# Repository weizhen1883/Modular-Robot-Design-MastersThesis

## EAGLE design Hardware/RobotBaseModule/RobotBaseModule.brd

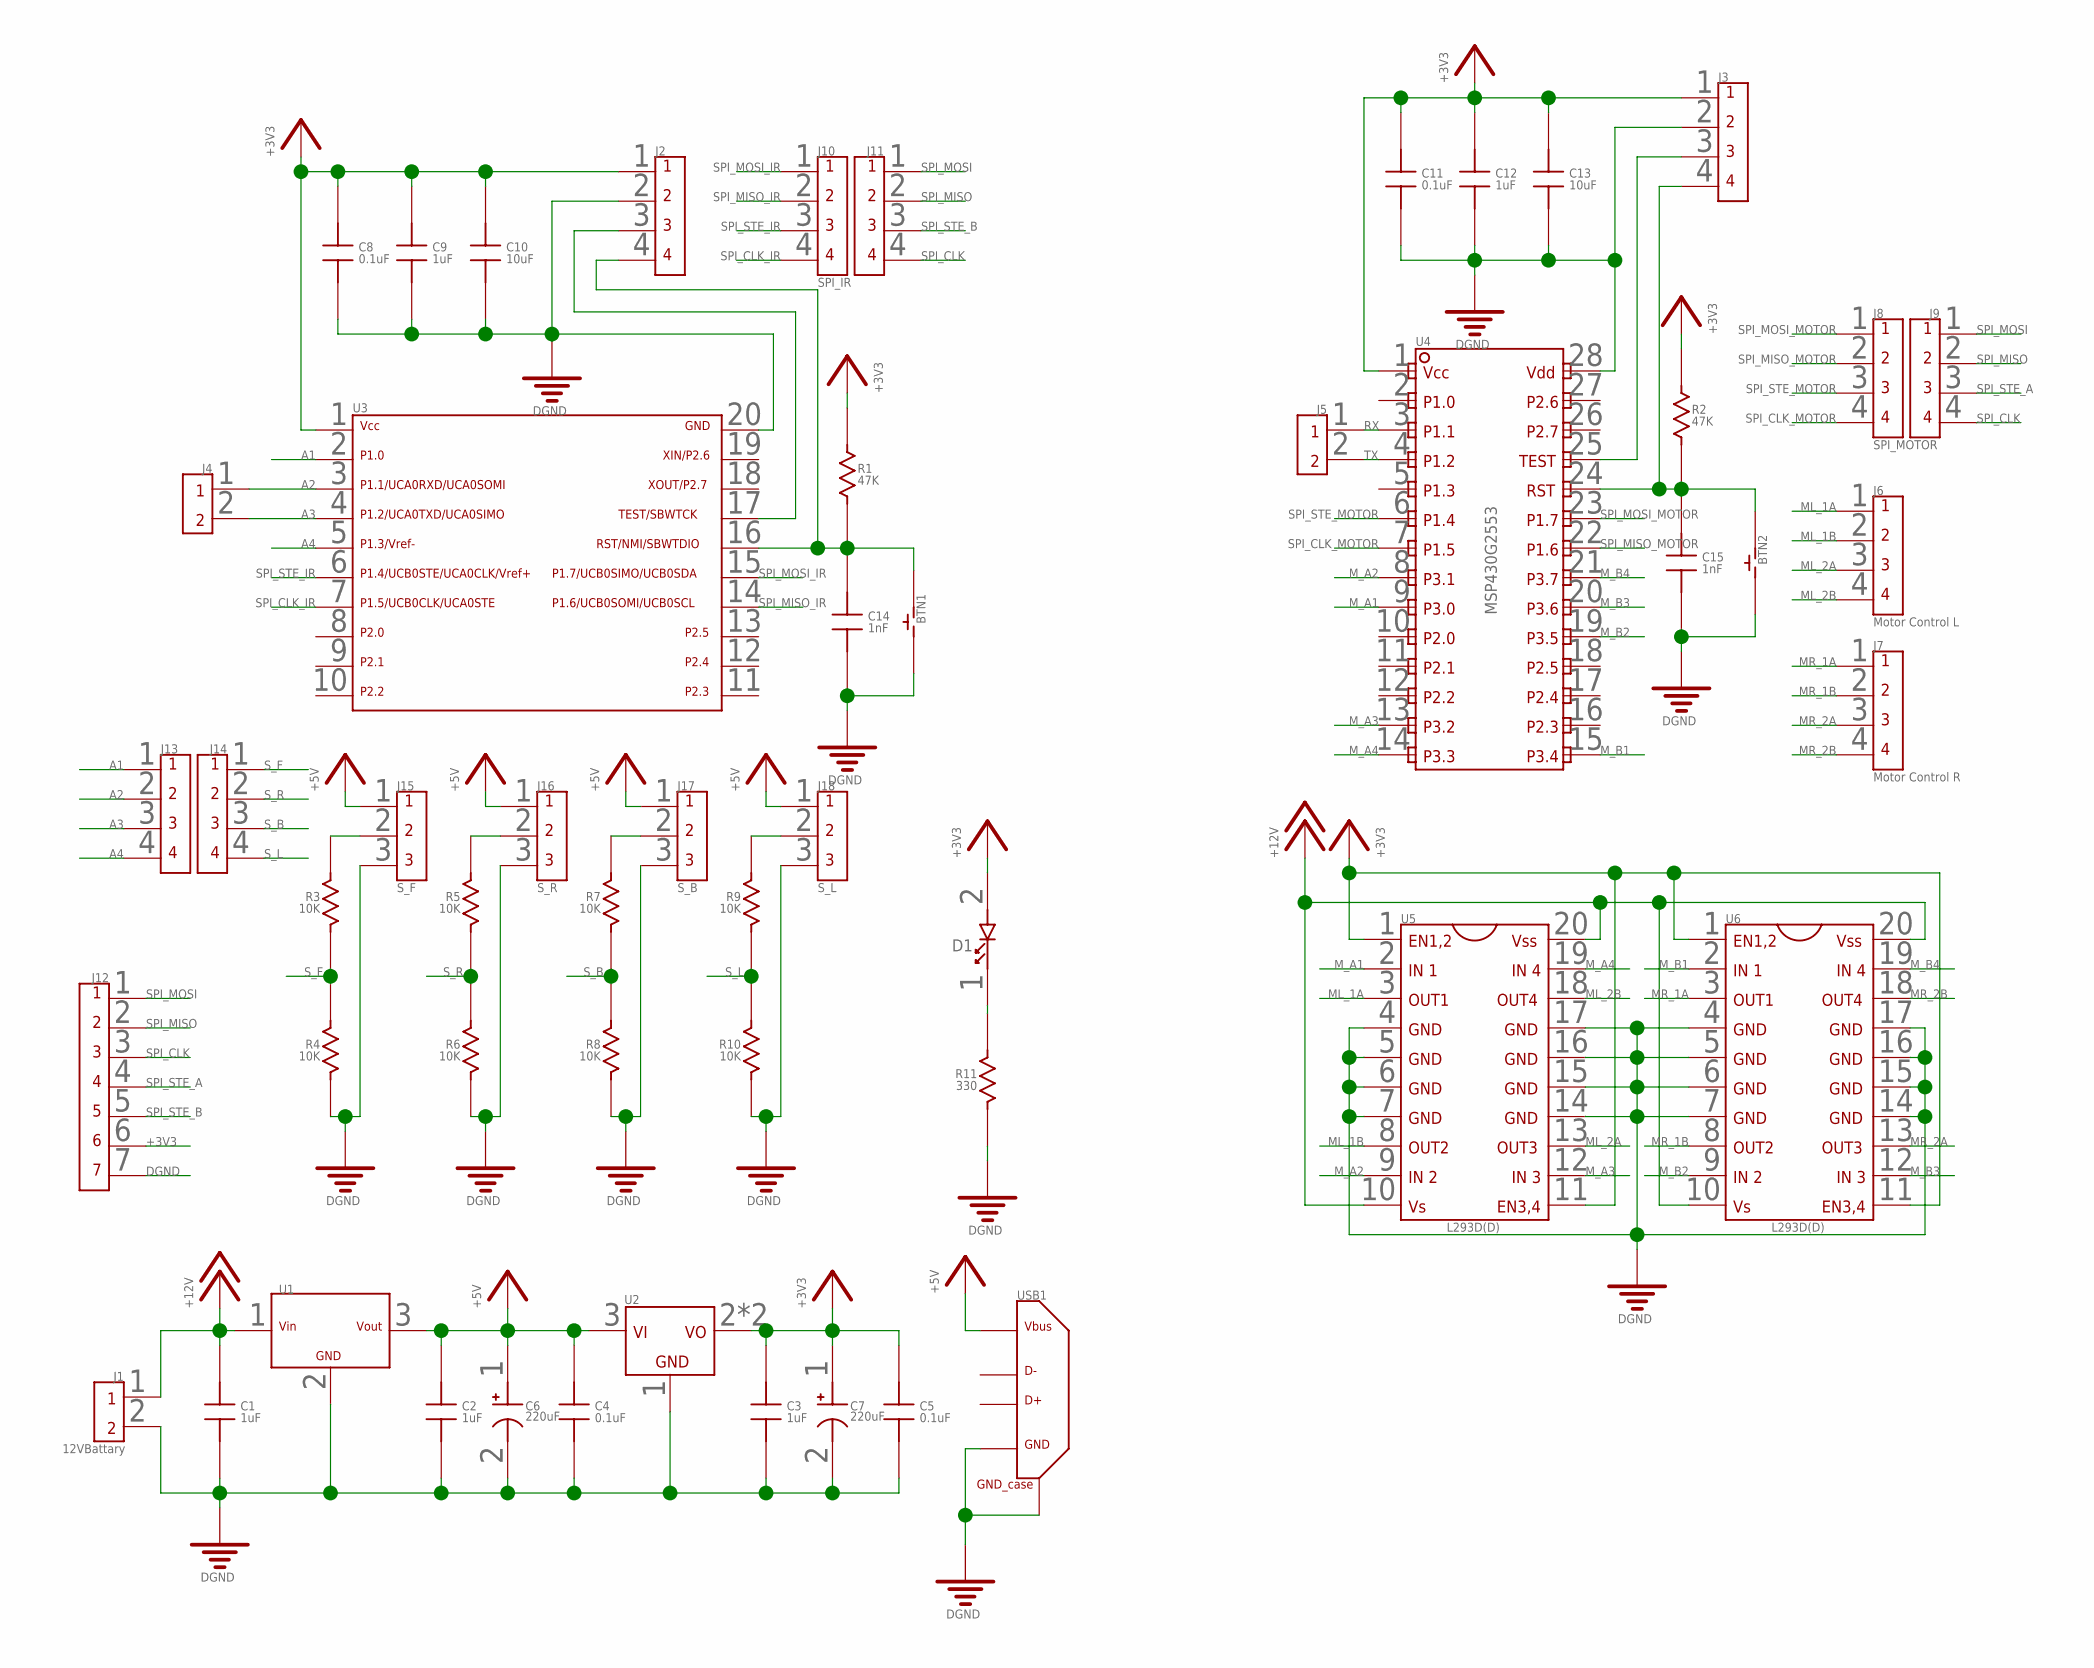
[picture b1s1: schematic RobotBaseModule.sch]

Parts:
BTN1, BTN2: BTN_NORMAL_OFF_6_3.5_SMD; BTN_6_3.5_SMD
C1, C2, C3, C9, C12: 1uF; 0805
C4, C5, C8, C11: 0.1uF; 0805
C6, C7: 220uF; CAP_830_830
C10, C13: 10uF; 0805
C14, C15: 1nF; 0805
D1: LED_0805; 0805DIODE
J1: 12VBattary; 2PIN_TERMBLOCK_PITCH5.08MM
J2, J3: 4PIN_HEADER_VERT_PITCH2.54MM_TH
J4, J5: 2PIN_HEADER_PITCH2.54MM_TH
J6: Motor Control L; 4PIN_HEADER_VERT_PITCH2.54MM_TH
J7: Motor Control R; 4PIN_HEADER_VERT_PITCH2.54MM_TH
J8: SPI_MOTOR; 4PIN_HEADER_PITCH2.54MM_TH
J9, J11, J13, J14: 4PIN_HEADER_PITCH2.54MM_TH
J10: SPI_IR; 4PIN_HEADER_PITCH2.54MM_TH
J12: 7PIN_HEADER_VERT_PITCH2.54MM_TH
J15: S_F; 3PIN_HEADER_VERT_PITCH2.54MM_TH
J16: S_R; 3PIN_HEADER_VERT_PITCH2.54MM_TH
J17: S_B; 3PIN_HEADER_VERT_PITCH2.54MM_TH
J18: S_L; 3PIN_HEADER_VERT_PITCH2.54MM_TH
R1, R2: 47K; 0805
R3, R4, R5, R6, R7, R8, R9, R10: 10K; 0805
R11: 330; 0805
U1: V78-2000R
U2: LM1117_SOT-223-4; SOT-233-4
U3: MSP430G2X53/G2X13_SSOP20; SSOP-20
U4: MSP430G2553; TSSOP-28
U5, U6: L293D(D)_ST_SMD; SOIC_20
USB1: USB-1.X/2.0-STANDARDTYPEA-TH; USB-A-TH

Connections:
+3V3: C3.1, C5.1, C7.1, C8.1, C9.1, C10.1, C11.1, C12.1, C13.1, D1.2, J2.1, J3.1, J12.6, R1.1, R2.1, U2.2 (VOUT), U2.4 (VOUT), U3.1, U4.1, U5.1, U5.11, U6.1, U6.11
+5V: C2.1, C4.1, C6.1, J15.1, J16.1, J17.1, J18.1, U1.3 (VOUT), U2.3 (VIN), USB1.1 (VBUS)
+12V: C1.1, J1.1, U1.1 (VIN), U5.10, U5.20, U6.10, U6.20
A1: J13.1, U3.2
A2: J4.1, J13.2, U3.3
A3: J4.2, J13.3, U3.4
A4: J13.4, U3.5
DGND: BTN1.2, BTN2.2, C1.2, C2.2, C3.2, C4.2, C5.2, C6.2, C7.2, C8.2, C9.2, C10.2, C11.2, C12.2, C13.2, C14.2, C15.2, J1.2, J2.2, J3.2, J12.7, J15.3, J16.3, J17.3, J18.3, R4.2, R6.2, R8.2, R10.2, R11.2, U1.2 (GND), U2.1 (GND), U3.20, U4.28, U5.4, U5.5, U5.6, U5.7, U5.14, U5.15, U5.16, U5.17, U6.4, U6.5, U6.6, U6.7, U6.14, U6.15, U6.16, U6.17, USB1.4 (GND), USB1.CASE1 (GND_CASE), USB1.CASE2 (GND_CASE)
ML_1A: J6.1, U5.3
ML_1B: J6.2, U5.8
ML_2A: J6.3, U5.13
ML_2B: J6.4, U5.18
MR_1A: J7.1, U6.3
MR_1B: J7.2, U6.8
MR_2A: J7.3, U6.13
MR_2B: J7.4, U6.18
M_A1: U4.9, U5.2
M_A2: U4.8, U5.9
M_A3: U4.13, U5.12
M_A4: U4.14, U5.19
M_B1: U4.15, U6.2
M_B2: U4.19, U6.9
M_B3: U4.20, U6.12
M_B4: U4.21, U6.19
unnamed: J3.3, U4.25
unnamed: J2.3, U3.17
unnamed: BTN1.1, C14.1, J2.4, R1.2, U3.16
unnamed: BTN2.1, C15.1, J3.4, R2.2, U4.24
unnamed: J15.2, R3.1
unnamed: D1.1, R11.1
unnamed: J16.2, R5.1
unnamed: J17.2, R7.1
unnamed: J18.2, R9.1
RX: J5.1, U4.3
SPI_CLK: J9.4, J11.4, J12.3
SPI_CLK_IR: J10.4, U3.7
SPI_CLK_MOTOR: J8.4, U4.7
SPI_MISO: J9.2, J11.2, J12.2
SPI_MISO_IR: J10.2, U3.14
SPI_MISO_MOTOR: J8.2, U4.22
SPI_MOSI: J9.1, J11.1, J12.1
SPI_MOSI_IR: J10.1, U3.15
SPI_MOSI_MOTOR: J8.1, U4.23
SPI_STE_A: J9.3, J12.4
SPI_STE_B: J11.3, J12.5
SPI_STE_IR: J10.3, U3.6
SPI_STE_MOTOR: J8.3, U4.6
S_B: J14.3, R7.2, R8.1
S_F: J14.1, R3.2, R4.1
S_L: J14.4, R9.2, R10.1
S_R: J14.2, R5.2, R6.1
TX: J5.2, U4.4

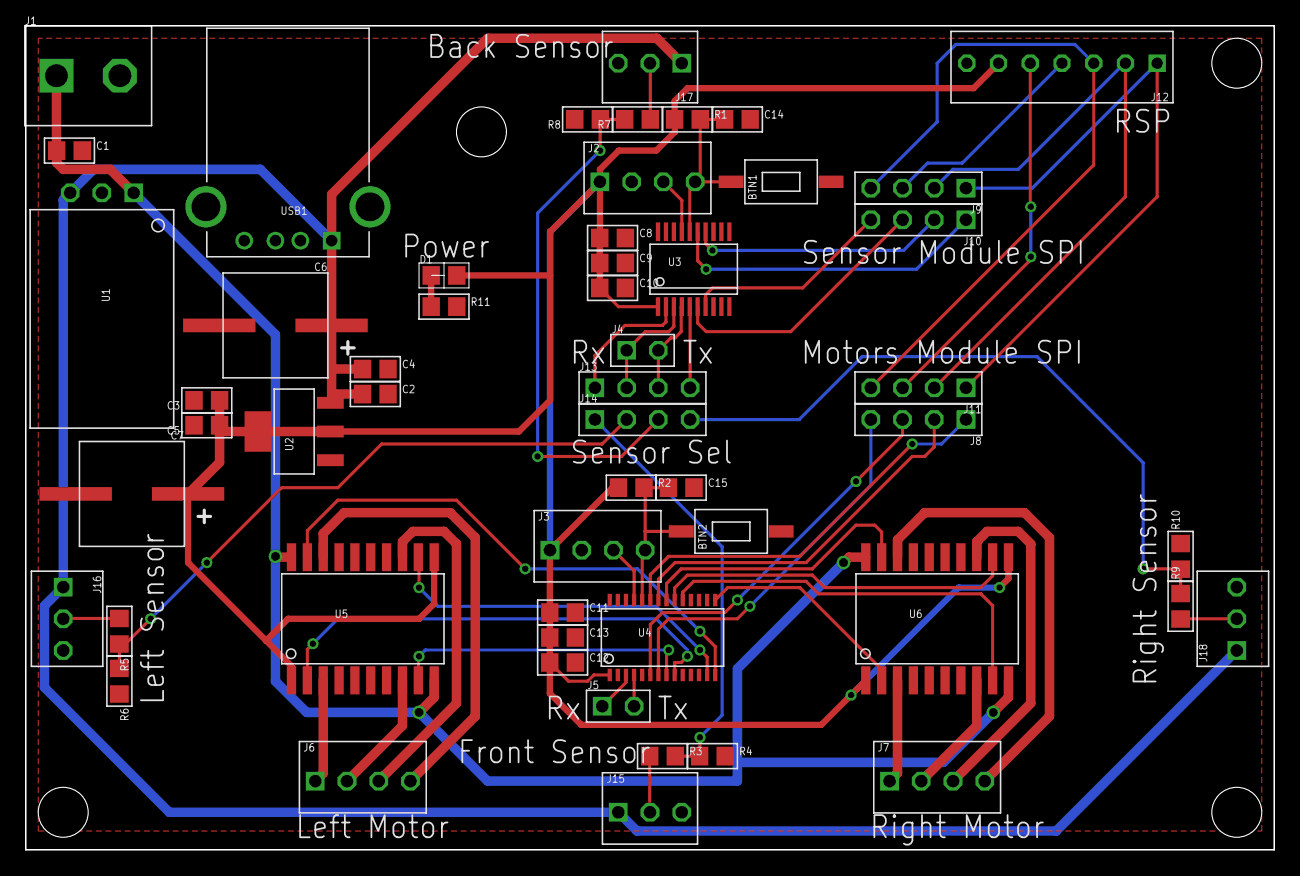
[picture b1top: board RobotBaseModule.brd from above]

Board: 2 copper layers, 100.0 x 66.0 mm, 54 parts (0 on the bottom side), 52 nets.

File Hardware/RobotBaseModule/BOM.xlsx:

Parts | Value | Footprint | Parts Number | Price | Quantity | Total
C1,C2,C3,C9,C12 | 1uF | 0805 | CL21F105ZOCNNNC | 0.1 | 5 | 0.5
C4,C5,C8,C11 | 0.1uF | 0805 | CL21F104ZBCNNNC | 0.1 | 4 | 0.4
C10,C13 | 10uF | 0805 | CL21F106ZQFNNNE | 0.14000000000000001 | 2 | 0.28000000000000003
C14,C15 | 1nF | 0805 | CL21C102JBCNNNC | 0.1 | 2 | 0.2
C6,C7 | 220uF | CAP830*830 | UWX0J221MCL1GB | 0.34 | 2 | 0.68
R1,R2 | 47KΩ | 0805 | RC2012F473CS | 0.1 | 2 | 0.2
R3,R4,R5,R6,R7,R8,R9,R10 | 10KΩ | 0805 | RC0805JR-0710KL | 0.1 | 8 | 0.8
R11 | 330Ω | 0805 | RC2012F331CS | 0.1 | 1 | 0.1
D1 |  | 0805 | LG R971-KN-1 | 0.26 | 1 | 0.26
U1 | V7805-2000R | V78-2000R | V7805-2000R | 10.84 | 1 | 10.84
U2 | LM1117-3.3V | SOT-233-4 | LM1117IMPX-3.3/NOPB | 1.04 | 1 | 1.04
U3 | MSP430G2553 | SSOP-20 | MSP430G2553IPW20R | 2.46 | 1 | 2.46
U4 | MSP430G2553 | TSSOP-28 | MSP430G2553IPW28R | 2.73 | 1 | 2.73
U5,U6 | L293DD | SOIC_20 | L293DD | 3.44 | 2 | 6.88
BTN1,BTN2 | SPST SMD | 6*3.5 |  | 0.15 | 2 | 0.3
USB1 | USB1.X/2.0 Standard TypeA TH | USB-A-TH |  | 0.1 | 1 | 0.1
J1 | 2pin 0.200" terminal block | 2PIN_TERMBLOCK_PITCH5.08MM | 1935161 | 0.37 | 1 | 0.37
J2,J3,J6,J7 | 4pin 0.100" header (single dir) | 4PIN_HEADER_VERT_PITCH2.54MM | 640454-4 | 0.18 | 4 | 0.72
J4,J5 | 2pin 0.100" header | 2PIN_HEADER_PITCH2.54MM |  | 0.1 | 2 | 0.2
J8,J9,J10,J11,J13,J14 | 4pin 0.100" header | 4PIN_HEADER_PITCH2.54MM |  | 0.1 | 6 | 0.60000000000000009
J12 | 7pin 0.100" header (single dir) | 7PIN_HEADER_VERT_PITCH2.54MM | 640456-7 | 0.27 | 1 | 0.27
J15,J16,J17,J18 | 3pin 0.100" header (single dir) | 3PIN_HEADER_VERT_PITCH2.54MM | 640454-3 | 0.16 | 1 | 0.16
 | CONN HOUS 3POS 0.100 |  | 0022013037 | 0.19 | 4 | 0.76
 | CONN HOUS 4POS 0.100 |  | 0022013047 | 0.2 | 4 | 0.8
 | CONN HOUS 7POS 0.100 |  | 0022013077 | 0.36 | 1 | 0.36
 |  |  |  |  | Total: | 29.19

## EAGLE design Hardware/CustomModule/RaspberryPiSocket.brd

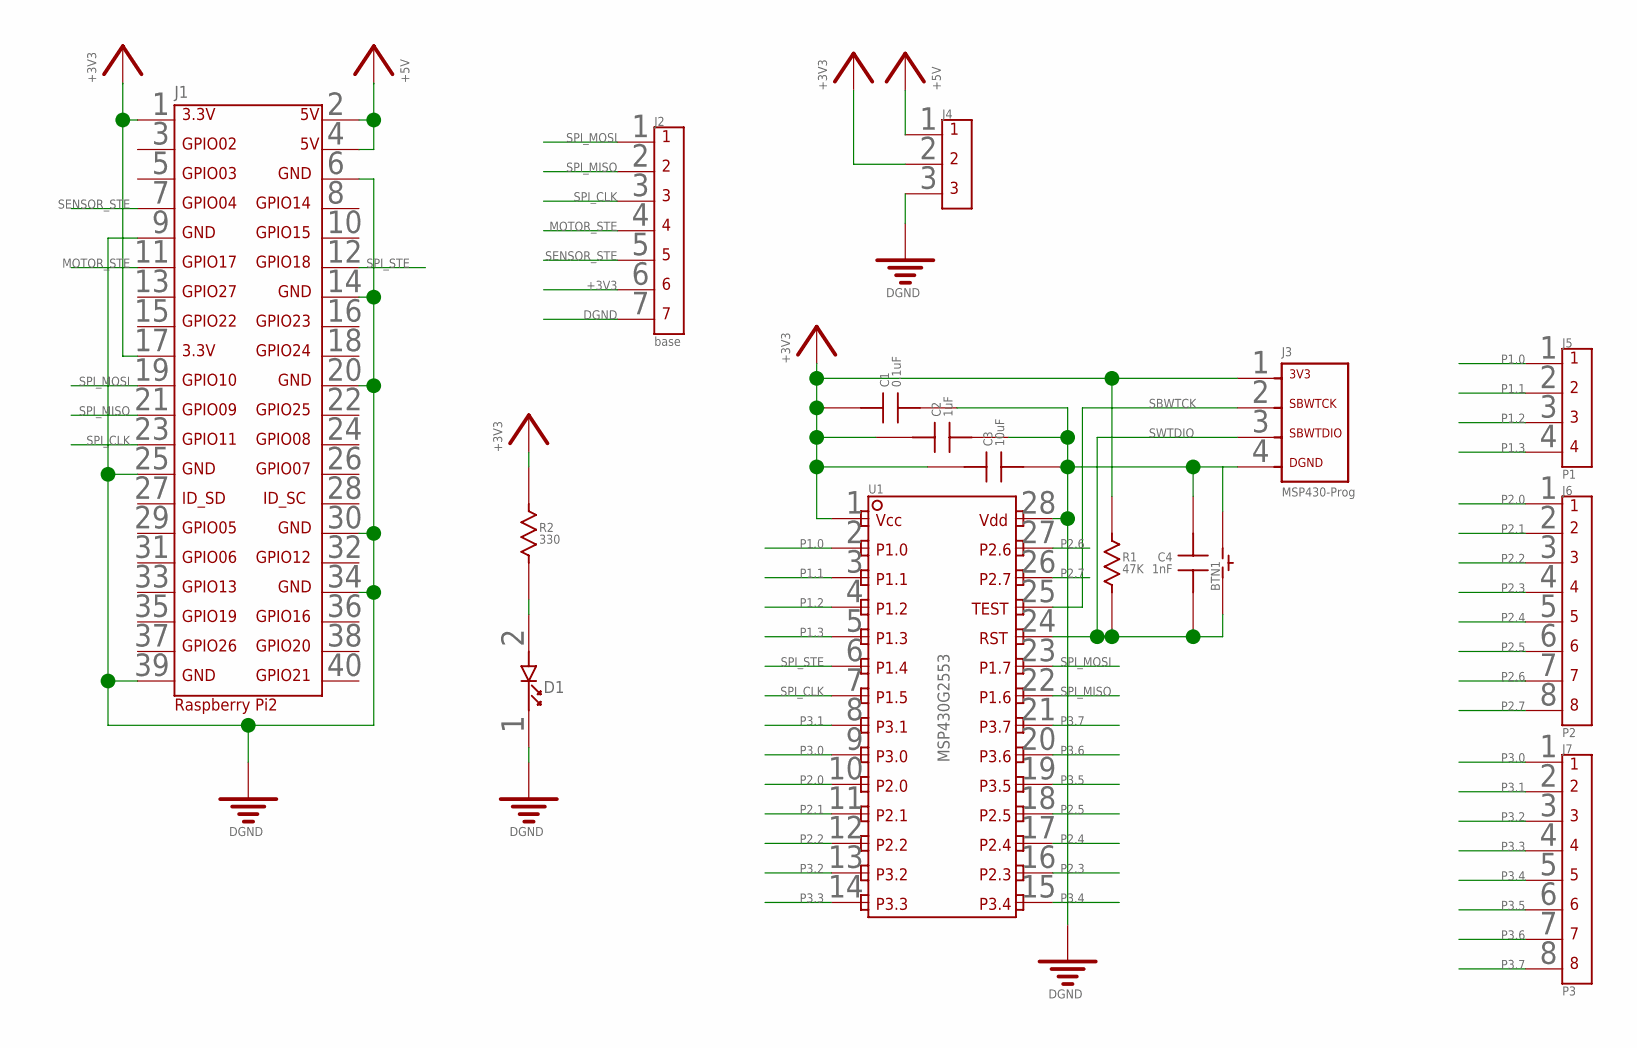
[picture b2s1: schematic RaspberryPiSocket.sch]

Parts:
BTN1: BTN_NORMAL_OFF_6_3.5_SMD; BTN_6_3.5_SMD
C1: 0.1uF; 0805
C2: 1uF; 0805
C3: 10uF; 0805
C4: 1nF; 0805
D1: LED_0805; 0805DIODE
J1: RPI2
J2: base; 7PIN_HEADER_VERT_PITCH2.54MM_TH
J3: MSP430-PROG_NORMAL; 4PIN_HEADER_PITCH2.54MM_TH
J4: 3PIN_HEADER_PITCH2.54MM_TH
J5: P1; 4PIN_HEADER_PITCH2.54MM_TH
J6: P2; 8PIN_HEADER_PITCH2.54MM_TH
J7: P3; 8PIN_HEADER_PITCH2.54MM_TH
R1: 47K; 0805
R2: 330; 0805
U1: MSP430G2553_24IO_28PIN_TSSOP; TSSOP-28

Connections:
+3V3: C1.1, C2.1, C3.1, J1.1, J1.17, J2.6, J3.1, J4.2, R1.1, R2.1, U1.1
+5V: J1.2, J1.4, J4.1
DGND: BTN1.2, C1.2, C2.2, C3.2, C4.1, D1.1, J1.6, J1.9, J1.14, J1.20, J1.25, J1.30, J1.34, J1.39, J2.7, J3.4, J4.3, U1.28
MOTOR_STE: J1.11, J2.4
unnamed: D1.2, R2.2
P1.0: J5.1, U1.2
P1.1: J5.2, U1.3
P1.2: J5.3, U1.4
P1.3: J5.4, U1.5
P2.0: J6.1, U1.10
P2.1: J6.2, U1.11
P2.2: J6.3, U1.12
P2.3: J6.4, U1.16
P2.4: J6.5, U1.17
P2.5: J6.6, U1.18
P2.6: J6.7, U1.27
P2.7: J6.8, U1.26
P3.0: J7.1, U1.9
P3.1: J7.2, U1.8
P3.2: J7.3, U1.13
P3.3: J7.4, U1.14
P3.4: J7.5, U1.15
P3.5: J7.6, U1.19
P3.6: J7.7, U1.20
P3.7: J7.8, U1.21
SBWTCK: J3.2, U1.25
SENSOR_STE: J1.7, J2.5
SPI_CLK: J1.23, J2.3, U1.7
SPI_MISO: J1.21, J2.2, U1.22
SPI_MOSI: J1.19, J2.1, U1.23
SPI_STE: J1.12, U1.6
SWTDIO: BTN1.1, C4.2, J3.3, R1.2, U1.24

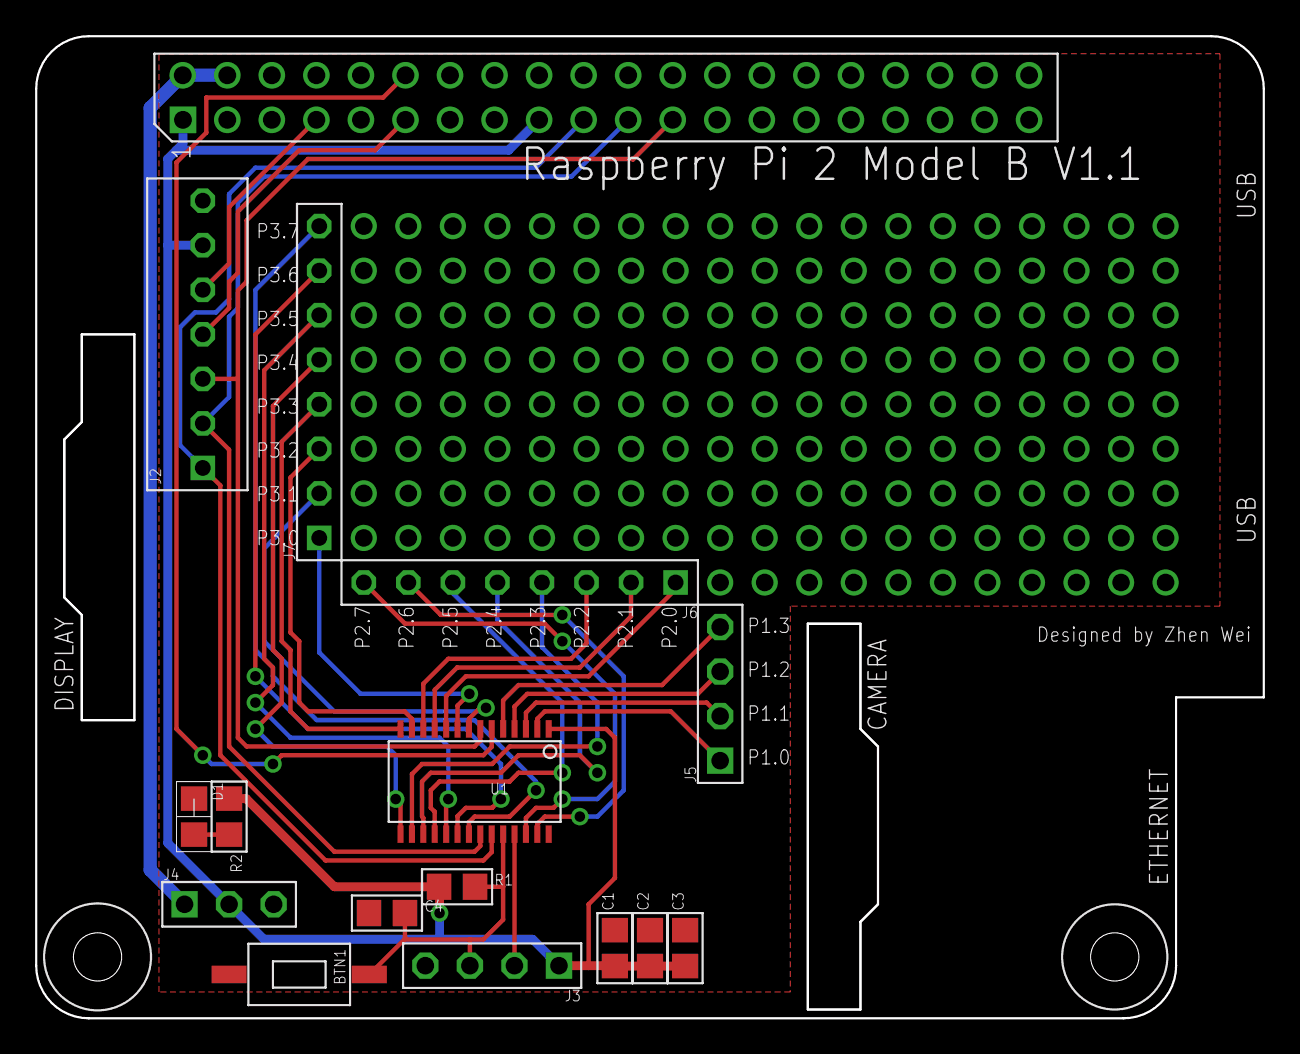
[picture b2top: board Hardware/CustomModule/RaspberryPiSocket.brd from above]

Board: 2 copper layers, 70.0 x 56.0 mm, 16 parts (0 on the bottom side), 32 nets.

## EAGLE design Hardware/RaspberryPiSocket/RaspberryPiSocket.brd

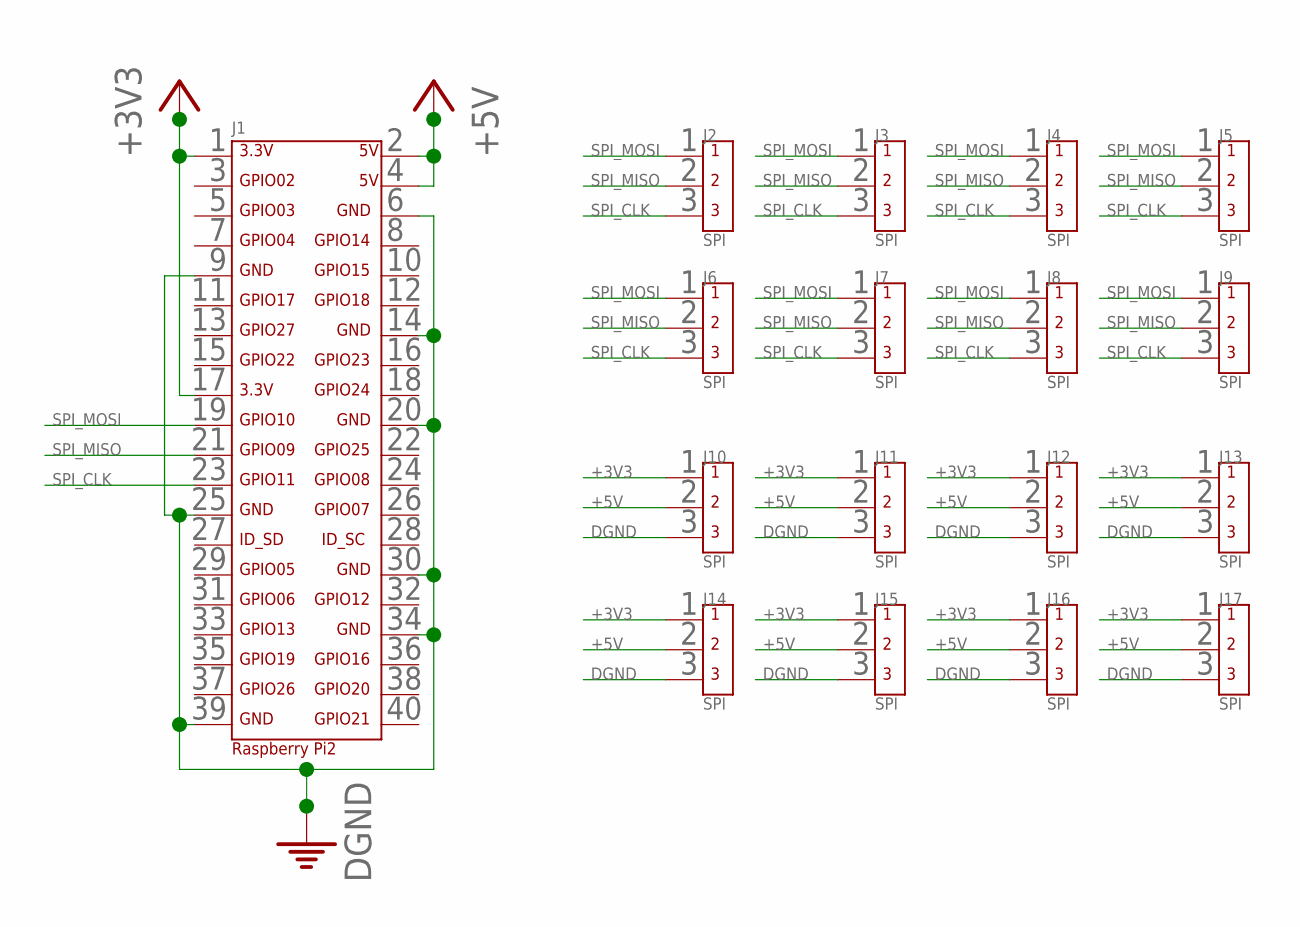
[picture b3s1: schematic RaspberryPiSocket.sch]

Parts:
J1: RPI2
J2, J3, J4, J5, J6, J7, J8, J9, J10, J11, J12, J13, J14, J15, J16, J17: SPI; CON_HEADER_3_100

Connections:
+3V3: J1.1, J1.17, J10.1, J11.1, J12.1, J13.1, J14.1, J15.1, J16.1, J17.1
+5V: J1.2, J1.4, J10.2, J11.2, J12.2, J13.2, J14.2, J15.2, J16.2, J17.2
DGND: J1.6, J1.9, J1.14, J1.20, J1.25, J1.30, J1.34, J1.39, J10.3, J11.3, J12.3, J13.3, J14.3, J15.3, J16.3, J17.3
SPI_CLK: J1.23, J2.3, J3.3, J4.3, J5.3, J6.3, J7.3, J8.3, J9.3
SPI_MISO: J1.21, J2.2, J3.2, J4.2, J5.2, J6.2, J7.2, J8.2, J9.2
SPI_MOSI: J1.19, J2.1, J3.1, J4.1, J5.1, J6.1, J7.1, J8.1, J9.1

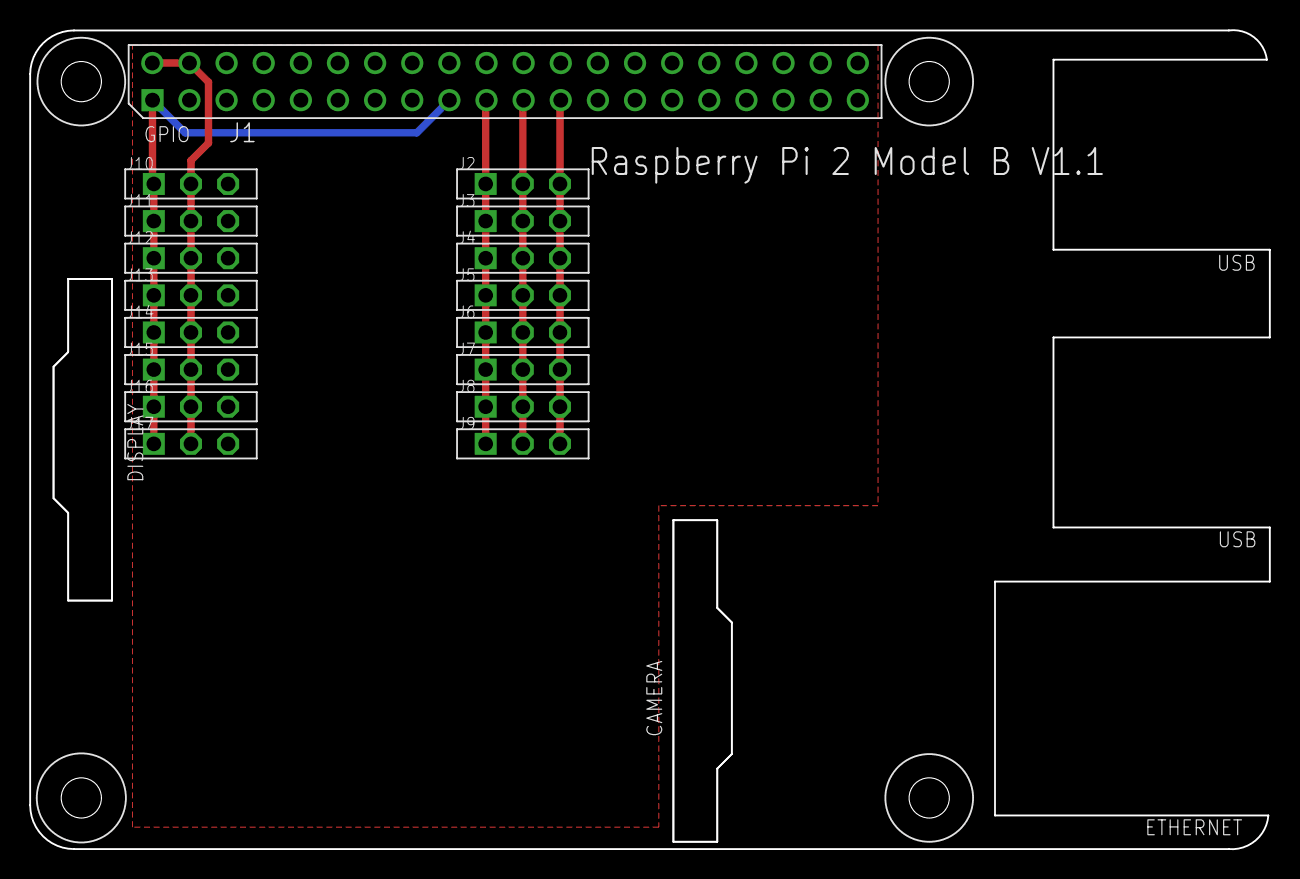
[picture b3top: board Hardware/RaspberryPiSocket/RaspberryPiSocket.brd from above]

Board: 2 copper layers, 84.8 x 56.0 mm, 17 parts (0 on the bottom side), 6 nets.

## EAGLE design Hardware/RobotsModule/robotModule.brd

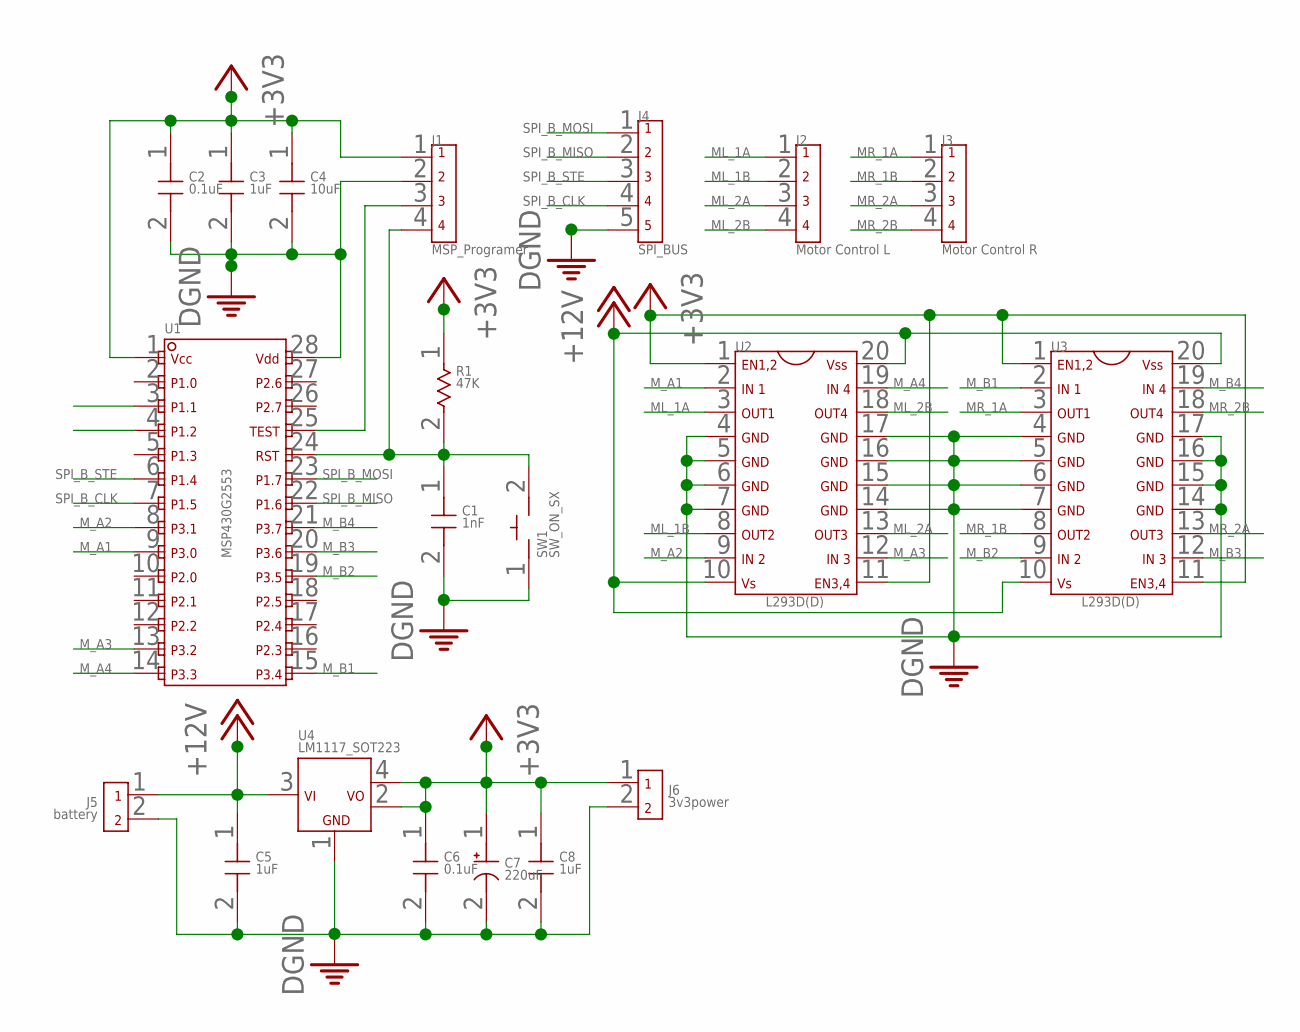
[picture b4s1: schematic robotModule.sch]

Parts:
C1: 1nF; 0805
C2, C6: 0.1uF; 0805
C3, C5, C8: 1uF; 0805
C4: 10uF; 0805
C7: 220uF; CAP_530_530
J1: MSP_Programer; CON_HEADER_4_100
J2: Motor Control L; CON_HEADER_4_100
J3: Motor Control R; CON_HEADER_4_100
J4: SPI_BUS; CON_HEADER_5_100
J5: battery; CON_HEADER_2_200
J6: 3v3power; CON_HEADER_2_100
R1: 47K; 0805
SW1: SW_ON_SX; SW_S
U1: MSP430G2553_24IO_28PIN_TSSOP; TSSOP_28
U2, U3: L293D(D)_ST_SMD; SOIC_20
U4: LM1117_SOT223; SOT_233_4

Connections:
+3V3: C2.1, C3.1, C4.1, C6.1, C7.1, C8.1, J1.1, J6.1, R1.1, U1.1, U2.1, U2.11, U3.1, U3.11, U4.2, U4.4
+12V: C5.1, J5.1, U2.10, U2.20, U3.10, U3.20, U4.3
DGND: C1.2, C2.2, C3.2, C4.2, C5.2, C6.2, C7.2, C8.2, J1.2, J4.5, J5.2, J6.2, SW1.1, U1.28, U2.4, U2.5, U2.6, U2.7, U2.14, U2.15, U2.16, U2.17, U3.4, U3.5, U3.6, U3.7, U3.14, U3.15, U3.16, U3.17, U4.1
ML_1A: J2.1, U2.3
ML_1B: J2.2, U2.8
ML_2A: J2.3, U2.13
ML_2B: J2.4, U2.18
MR_1A: J3.1, U3.3
MR_1B: J3.2, U3.8
MR_2A: J3.3, U3.13
MR_2B: J3.4, U3.18
MSP430REST: C1.1, J1.4, R1.2, SW1.2, U1.24
M_A1: U1.9, U2.2
M_A2: U1.8, U2.9
M_A3: U1.13, U2.12
M_A4: U1.14, U2.19
M_B1: U1.15, U3.2
M_B2: U1.19, U3.9
M_B3: U1.20, U3.12
M_B4: U1.21, U3.19
unnamed: J1.3, U1.25
SPI_B_CLK: J4.4, U1.7
SPI_B_MISO: J4.2, U1.22
SPI_B_MOSI: J4.1, U1.23
SPI_B_STE: J4.3, U1.6

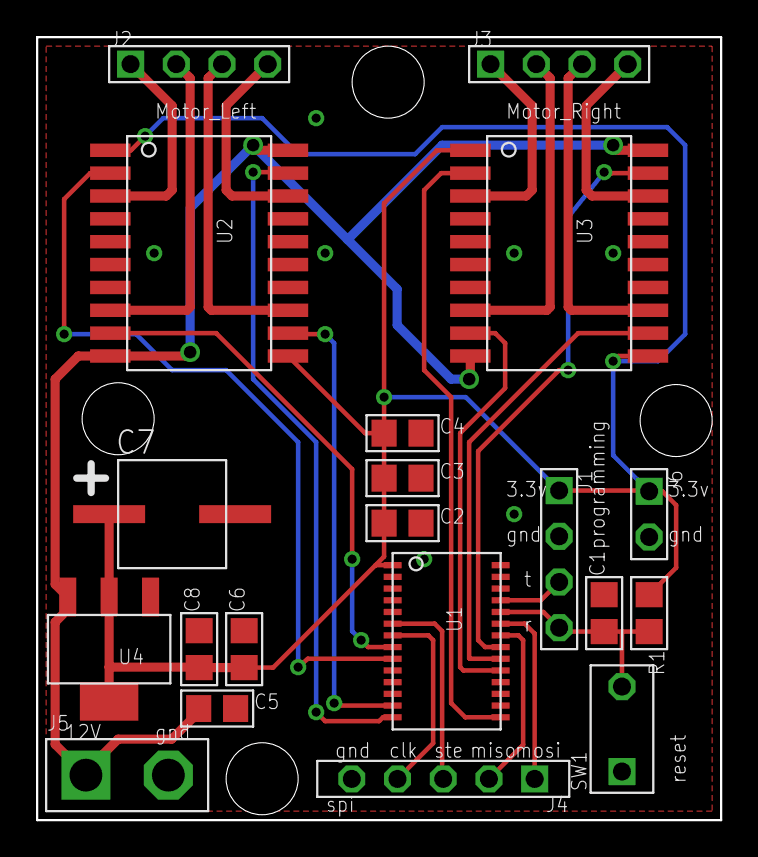
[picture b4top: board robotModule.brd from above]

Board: 2 copper layers, 38.0 x 43.5 mm, 20 parts (0 on the bottom side), 25 nets.

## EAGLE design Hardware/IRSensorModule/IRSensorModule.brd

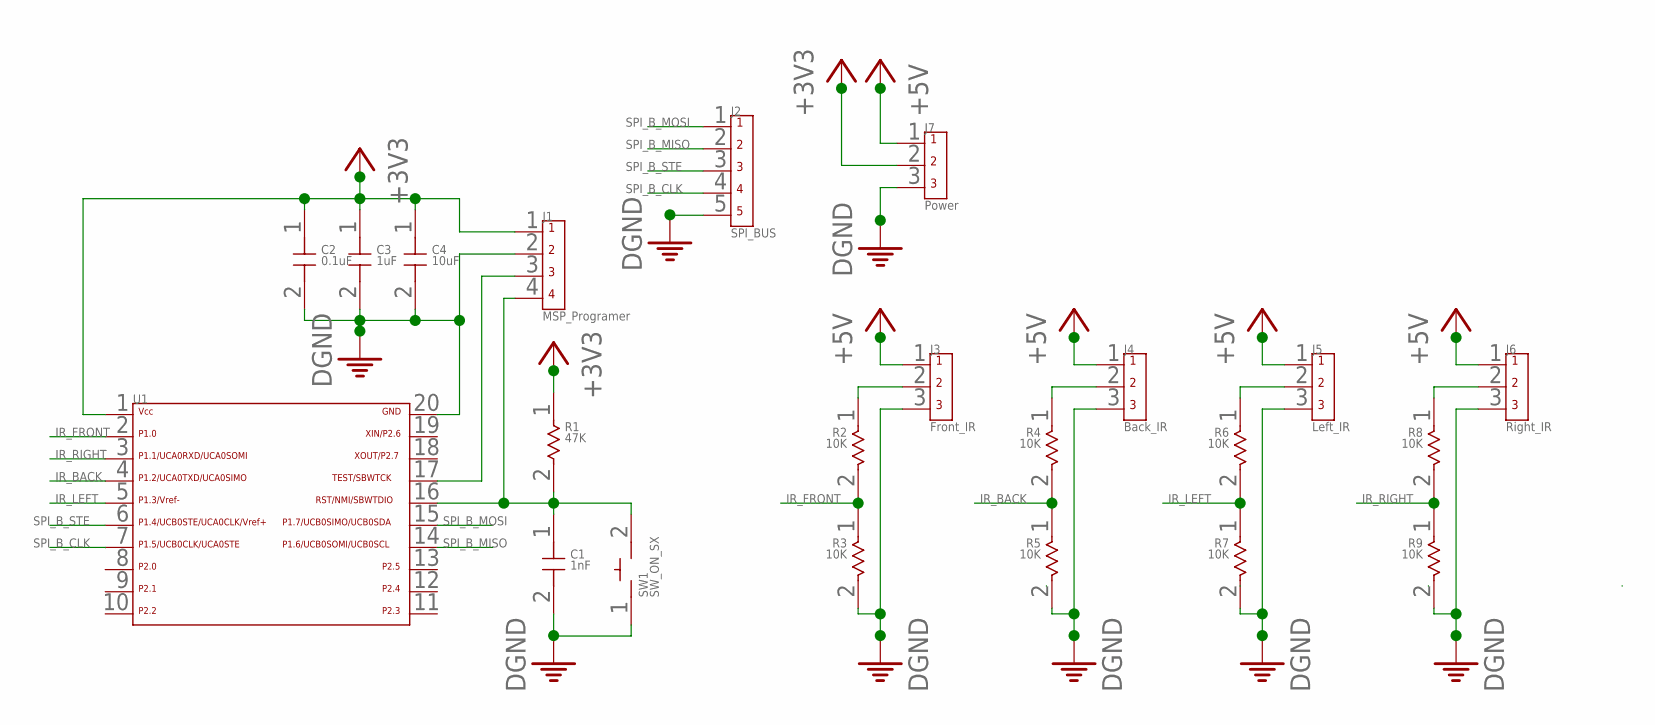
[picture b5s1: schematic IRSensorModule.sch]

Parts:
C1: 1nF; 0805
C2: 0.1uF; 0805
C3: 1uF; 0805
C4: 10uF; 0805
J1: MSP_Programer; CON_HEADER_4_100
J2: SPI_BUS; CON_HEADER_5_100
J3: Front_IR; CON_HEADER_3_100
J4: Back_IR; CON_HEADER_3_100
J5: Left_IR; CON_HEADER_3_100
J6: Right_IR; CON_HEADER_3_100
J7: Power; CON_HEADER_3_100
R1: 47K; 0805
R2, R3, R4, R5, R6, R7, R8, R9: 10K; 0805
SW1: SW_ON_SX; SW_S
U1: MSP430G2X53/G2X13_20PIN; SSOP-20

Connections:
+3V3: C2.1, C3.1, C4.1, J1.1, J7.2, R1.1, U1.1
+5V: J3.1, J4.1, J5.1, J6.1, J7.1
DGND: C1.2, C2.2, C3.2, C4.2, J1.2, J2.5, J3.3, J4.3, J5.3, J6.3, J7.3, R3.2, R5.2, R7.2, R9.2, SW1.1, U1.20
IR_BACK: R4.2, R5.1, U1.4
IR_FRONT: R2.2, R3.1, U1.2
IR_LEFT: R6.2, R7.1, U1.5
IR_RIGHT: R8.2, R9.1, U1.3
MSP430REST: C1.1, J1.4, R1.2, SW1.2, U1.16
unnamed: J1.3, U1.17
unnamed: J3.2, R2.1
unnamed: J4.2, R4.1
unnamed: J5.2, R6.1
unnamed: J6.2, R8.1
SPI_B_CLK: J2.4, U1.7
SPI_B_MISO: J2.2, U1.14
SPI_B_MOSI: J2.1, U1.15
SPI_B_STE: J2.3, U1.6

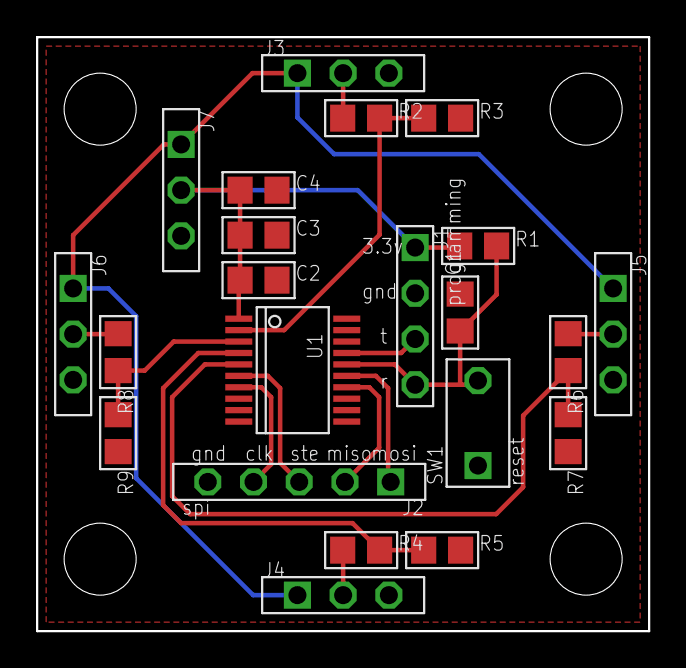
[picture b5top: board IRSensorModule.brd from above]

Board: 2 copper layers, 34.0 x 33.0 mm, 22 parts (0 on the bottom side), 17 nets.

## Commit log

2016-01-22 create the folders
2016-01-22 move the current msplib code into the resp
2016-01-22 the firmware for Motor_module is ready for test
2016-01-22 the rsp motor lib
2016-01-22 the motor module is done and tested
2016-01-25 starting test the IR sensor module
2016-01-29 the IR sensor module firmware closely done
2016-01-29 done the rasp lib for ir sensor
2016-02-01 Hardware V1.0: Upload all of the files has been done
2016-02-01 Hardware V2.0: The base module is ready for test
2016-02-01 Hardware V2.0:
2016-02-03 change some control code
2016-02-03 start working on the Software
2016-02-11 change the IR sensor side
2016-02-12 Obstacle Avoidance: the robot can go and stop when it sence the obstacles
2016-02-12 the base module has been test and most of the feature works, but the two in one spi port still has issues
2016-02-12 the custom Module is ready for testing
2016-02-13 the obstacle aboidance example project has been done
2016-02-19 make the makefile works
2016-02-24 start working on the wall following
2016-03-10 change the wall following example
2016-03-15 add the out corner figure
2016-03-15 remove the raspberry pi socket which will instand by custom module
2016-03-15 fix the time delay in rsplib
2016-03-16 fix the example issue
2016-04-29 make the final changes
